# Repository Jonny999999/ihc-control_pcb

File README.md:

Repo for designing a custom pcb that controlls the electrical components of an IHC-Tractor.

# TOC
- [Links](#links)
- [Overview](#overview)
- [Open Schematic and Layout](#open-schematic-and-layout)
- [Connector Pin-assignment](#connector-pin-assignment)
  * [New Connectors](#new-connectors)
  * [Old Connectors](#old-connectors)
- [I/O List](#i-o-list)
  * [Switches](#switches)
  * [Relays](#relays)
- [Instructions (milling process)](#instructions--milling-process-)
  * [Step 1: export files](#step-1--export-files)
  * [Step 2: generate gcode (holes, traces, outline)](#step-2--generate-gcode--holes--traces--outline-)
  * [Step 3: generate gcode (engraving text)](#step-3--generate-gcode--engraving-text-)
  * [Step 4: mill outline](#step-4--mill-outline)
  * [Step 5: post processing](#step-5--post-processing)
- [Notes for next version (pcb design)](#notes-for-next-version--pcb-design-)
- [Notes for next pcb (milling)](#notes-for-next-pcb-milling)
  * [CNC-Control (WinPC-NC)](#cnc-control--winpc-nc-)
    + [Parameters](#parameters)
    + [Occurred problems](#occurred-problems)
  * [G-code generation (pcb2gcode)](#g-code-generation--pcb2gcode-)
    + [Notes for next time](#notes-for-next-time-)
    + [Gerber export (kicad)](#gerber-export--kicad-)

# Links
- Project documentation: https://pfusch.zone/control-pcb
- Firmware repo: https://github.com/Jonny999999/ihc-control_fw

# Overview
### Schematic
[pcb-ihc_schem_v4-milled-v1.1.pdf](/kicad/export/pcb-ihc_schem_v4-milled-v1.1.pdf)

### PCB-layout

# Open Schematic and Layout
Install kicad and open /kicad/pcb-ihc_kicad.kicad_pro  

For quickly viewing the current schematic and layout without installing kicad see exported files in
`kicad/export` or complete documentation at https://pfusch.zone

# Connector Pin-assignment
## New Connectors
See plan in firmware repo: 
https://github.com/Jonny999999/ihc-control_fw/blob/master/connection-plan.pdf

## Old Connectors
### 2 Pole connector 6mm2:
- 1: Starter motor (9)
- 2: Glowplug

### 6 Pole PC (3)
- 1: empty
- 2: Front light right, left (top right)
- 2a: Switch brakelight LS 1/2
- 3: Horn 1/2
- 3a Switch brakelight LS 2/2
- 4: Light left AL, right AR (bottom right)

### 6 Pole PB (2)
- 1: (20) Starter motor (relay) (top left)
- 2: (22) Fuel sensord
- 3: (24) Horn 2/2
- 4: (26) Oil pressure (switch to gnd)
- 5: (28) Temperature sensor
- 6: (30) Voltage regulator alternator (?)

### 6 Pole PA (1)
- 1: (31,32) FD sidelight -> trailer connector
- 2: (37) LB LB Light left -> trailer connector
- 3: (90) Side light BR
- 4: (88) Side light BL
- 5: (43, 42) FA -> trailer connector
- 6: (48) LA light left -> trailer connector

# I/O List
List of required I/O pins for planning the board
## Switches
### Switch to GND (pullup input)
- S_Warning Lights
- S_TurnLeft  toggle
- S_TurnRight toggle
- S_HighBeam  momentary
- S_Warning Lights  toggle
- S_Horn

### Switch to 12V (pulldown input)
- S_ParkingLight
- S_LowBeam
- S_Brake

### Notes
- S_worklight !!! no input left?!

## Relays
- K_BlinkLeft
- K_BlinkRight
- K_ParkingLight
- K_LowBeam
- K_HighBeam
- K_Horn

# Instructions (milling process)
Machine used: Stepcraft 420
## Step 1: export files
- Kicad: Export/plot pcb to gerber files
  Note: Also export User1 layer (includes text for engraving)
- Kicad: Generate drill file
```
back=./in/pcb-ihc_kicad-B_Cu.gbr
front=./in/pcb-ihc_kicad-F_Cu.gbr
outline=./in/pcb-ihc_kicad-Edge_Cuts.gbr
drill=./in/pcb-ihc_kicad-PTH.drl
see config file: pcb2gcode/millproject
```

## Step 2: generate gcode (holes, traces, outline)
- run pcb2gcode: `ihc-control_pcb/pcb2gcode> pcb2gcode`  
  will use millproject file for parameters as default config

## Step 3: generate gcode (engraving text)
- Kicad: moved text to be engraved into pcb on separate layer (User1)
- Also export/plot User1 layer with other gerber files
- Use separate millproject_text parameter file with pcb2gcode
  `pcb2gcode --config millproject_text`
NOTE: also include outline and maybe front in that millproject, even though that output is not used. It is necessary that the origin fits, otherwise there will be an offset!
- The trick was to use a negative offest (almost half the line width) to get more or less clean characters
- Generates pcb2gcode/out/text/back.ngc
Note: check if there is an offset/scaling issue to other files (back, drill). last time text got engraved into traces even though it matched on the other side

## Step 4: mill outline
Was not necessary in this case because size already matched

## Step 5: post processing
- Slightly smooth copper layer of pcb using grinding wool
- Drill holes for big 4mm2 2-pin terminals to 1.5mm if drilled with just 1mm on cnc

# Notes for next version (pcb design)
- Add resistor and diode for slowly charging the input capacitor (limit charging current)
- Add diode and/or jumper for isp programmer. Noticed that current is flowing from board 5v to programmer (input resistor got hot - only when programme connected) (alternatively jumper on programmer can be used for this...)
- ADD FUSES
  - Add fuse for 12v supply to 5v regulator
  - Fuses for mosfets?
  - Fuses for relay?
- Add mounting holes / at least make some space for third hole
- Slightly smaller size for easier cnc-milling

# Notes for next pcb milling
## CNC-Control (WinPC-NC)
### Parameters
- WinPC-NC has weird default z coorinates direction
  => **Z coordinates have to be inverted (!!!!!)** (otherwise will crash)
  -> parameters -> dateiformat -> z-koordinaten invertieren
- Change units to mm/min instead of default mm/s
### Occurred problems
- Problem Stepper not moving, only producing noise, but winpc-nc actually thinks that it moved coordinates - especially happened for Z-Axis
  - Solution 1: remove top section of gcode (simple G1 commands worked - see gcode generated with estlcam that is compatible)
  - Solution 2: switch from windows in Virtualbox to native windows

## G-code generation (pcb2gcode)
### notes for next time:
TODO: merge this section with milling instructions?
- Text engraving: slightly reduce Z depth 
- Zero Z-axis on multiple places: 
  At 2 edges pcb material was apparently lower, thus only scratched the surface -> had to mill again
- Zero-XY NOT at file origin! (the offset is caused by outline cutter diameter) 
  - 1. Load outline gcode, zero x,y next to border (note offset) 
  - 2. Confirm with moving on other side of pcb
- Make screenshot of absolute coordinates of origin (in case of accidential shift / position loss)
- Check position before drilling holes
- Fixing the pcb: Screws around the pcb are probably enough (check bend)
- When generating gcode for text separately, also include at least outline, otherwise there is an offset (origin makes no sense)

### Gerber export (kicad)
- design pcb slightly smaller for more tolerance...
- define custom origin 
  => tried this, setting "drill/place file origin" and tick the checkbox at plot, but had no effect to pcb2gcode in any way
- check if origin is the same in every gerber/gcode file (verify with gcode viewer?)

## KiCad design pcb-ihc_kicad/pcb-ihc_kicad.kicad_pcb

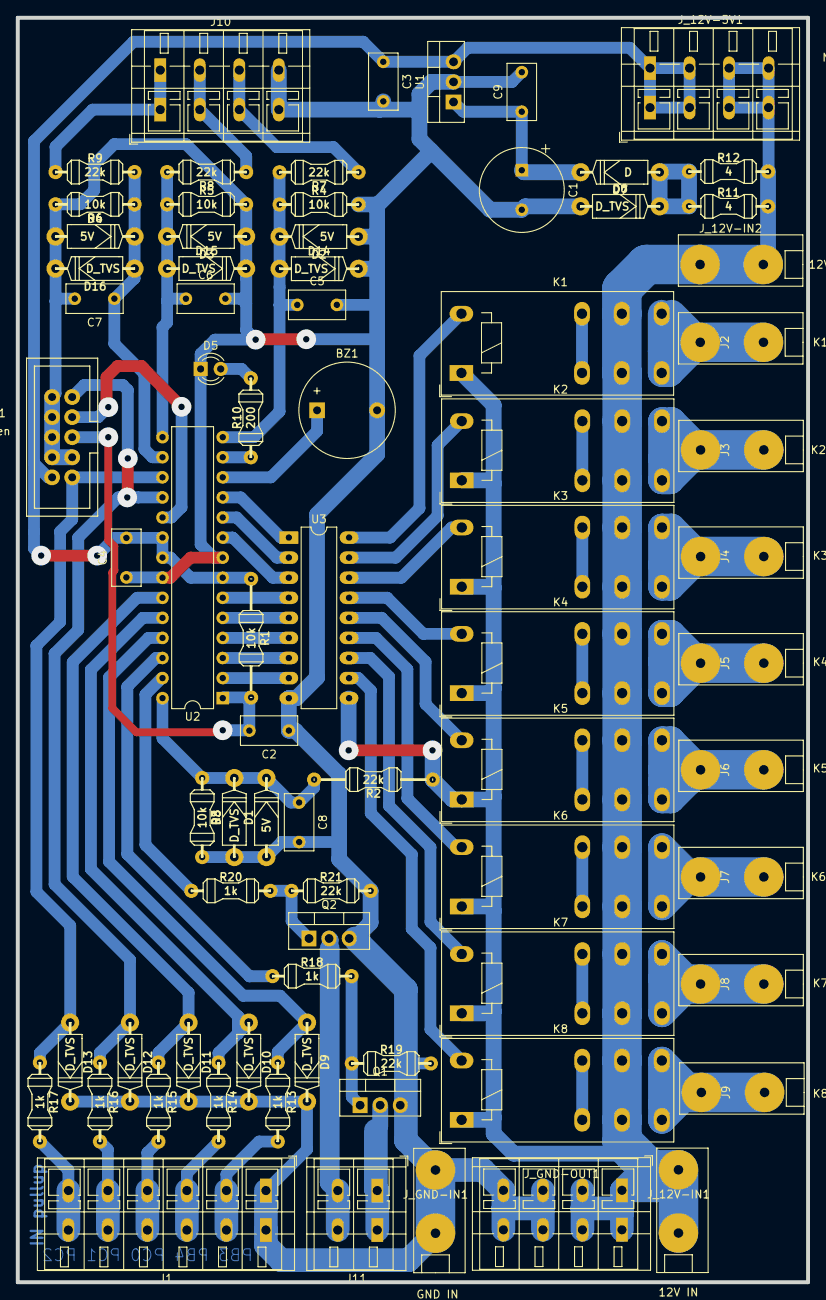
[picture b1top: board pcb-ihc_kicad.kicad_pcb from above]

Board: 2 copper layers, 100.0 x 160.0 mm, 77 parts (0 on the bottom side), 57 nets.

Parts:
BZ1: Buzzer - PD6; Buzzer_12x9.5RM7.6
C1: 100uF; CP_Radial_Tantal_D10.5mm_P5.00mm
C2, C3, C4, C5, C6, C7, C8: 100nF; C_Rect_L7.0mm_W3.5mm_P5.00mm
C9: 0.3uF; C_Rect_L7.0mm_W3.5mm_P5.00mm
D1, D2, D3, D4: 5V; my_D10_11
D5: LED - PD7; LED_D3.0mm
D6, D8, D9, D10, D11, D12, D13, D14, D15, D16: D_TVS; my_D10_11
D7: D; my_D10_11
J1: D-IN with pullup; TerminalBlock_WAGO_236-406_1x06_P5.00mm_45Degree
J2: K1 - PD5; my_KlemmeWago2604-single
J3: K2 - PB7; my_KlemmeWago2604-single
J4: K3 - PB6; my_KlemmeWago2604-single
J5: K4 - PD4; my_KlemmeWago2604-single
J6: K5 - PD3; my_KlemmeWago2604-single
J7: K6 - PD2; my_KlemmeWago2604-single
J8: K7 - PD1; my_KlemmeWago2604-single
J9: K8 - PD0; my_KlemmeWago2604-single
J10: D-IN with pulldown; TerminalBlock_WAGO_236-404_1x04_P5.00mm_45Degree
J11: 2x N-Mosfet; TerminalBlock_WAGO_236-402_1x02_P5.00mm_45Degree
J_12V-5V1: 2x 5V out, 2 x 12V out; TerminalBlock_WAGO_236-404_1x04_P5.00mm_45Degree
J_12V-IN1: 12V IN; my_KlemmeWago2604-single
J_12V-IN2: 12V IN (support); my_KlemmeWago2604-single
J_GND-IN1: GND IN; my_KlemmeWago2604-single
J_GND-OUT1: 2x GND out, 2x 12V out; TerminalBlock_WAGO_236-404_1x04_P5.00mm_45Degree
J_ISP-Programmer1: Conn_02x05_Odd_Even; my_wannenstecker_2x5
K1, K2, K3, K4, K5, K6, K7, K8: RT314A24; Relay_SPDT_Schrack-RT1-16A-FormC_RM5mm
Q1, Q2: IRFZ24N; TO-220-3_Vertical
R1: 10k; my_R15-long
R2: 22k; my_R15-long
R3, R4, R5, R6: 10k; my_R10
R7, R8, R9, R19, R21: 22k; my_R10
R10: 200; my_R10
R11, R12: 4; my_R10
R13, R14, R15, R16, R17, R18, R20: 1k; my_R10
U1: LM7805_TO220; TO-220-3_Vertical
U2: ATmega8-16P; DIP-28_W7.62mm
U3: ULN2803A; DIP-18_W7.62mm_LongPads

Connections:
+5V: C3.1, C4.2, J_12V-5V1.1, J_12V-5V1.2, J_ISP-Programmer1.2, R1.1, U1.3 (VO), U2.7 (VCC), U2.20 (AVCC), U2.21 (AREF)
+12V: J_12V-5V1.3, J_12V-5V1.4, J_12V-IN1.1, J_12V-IN2.1, J_GND-OUT1.1, J_GND-OUT1.2, K1.11, K1.A1, K2.11, K2.A1, K3.11, K3.A1, K4.11, K4.A1, K5.11, K5.A1, K6.11, K6.A1, K7.11, K7.A1, K8.11, K8.A1, R2.1, R11.2, R12.2, U3.10 (COM)
/Analog U_supply: C8.1, D1.1 (K), D8.1 (A1), R2.2, R3.1, U2.28 (PC5)
/IN pulldown 1: C5.1, D2.1 (K), D14.2 (A2), R4.1, R7.2, U2.14 (PB0)
/IN pulldown 2: C6.1, D3.1 (K), D15.2 (A2), R5.1, R8.2, U2.15 (PB1)
/IN pulldown 3: C7.1, D4.1 (K), D16.2 (A2), R6.1, R9.2, U2.16 (PB2)
/IN pullup 1: D13.2 (A2), J_ISP-Programmer1.1, R17.1, U2.17 (PB3)
/IN pullup 2: D12.2 (A2), J_ISP-Programmer1.9, R16.1, U2.18 (PB4)
/IN pullup 3: D11.2 (A2), R15.1, U2.23 (PC0)
/IN pullup 4: D10.2 (A2), R14.1, U2.24 (PC1)
/IN pullup 5: D9.2 (A2), R13.1, U2.25 (PC2)
/ISP-Reset: C2.2, J_ISP-Programmer1.5, R1.2, U2.1 (PC6/~RESET)
/ISP-SCK: J_ISP-Programmer1.7, U2.19 (PB5)
/Mosfet 1: R18.1, U2.26 (PC3)
/Mosfet 2: R20.1, U2.27 (PC4)
/ULN-I1: U2.11 (PD5), U3.1 (I1)
/ULN-I2: U2.10 (PB7/XTAL2), U3.2 (I2)
/ULN-I3: U2.9 (PB6/XTAL1), U3.3 (I3)
/ULN-I4: U2.6 (PD4), U3.4 (I4)
/ULN-I5: U2.5 (PD3), U3.5 (I5)
/ULN-I6: U2.4 (PD2), U3.6 (I6)
/ULN-I7: U2.3 (PD1), U3.7 (I7)
/ULN-I8: U2.2 (PD0), U3.8 (I8)
/buzzer: BZ1.1 (-), U2.12 (PD6)
/led: R10.1, U2.13 (PD7)
GND: BZ1.2 (+), C1.2, C2.1, C3.2, C4.1, C5.2, C6.2, C7.2, C8.2, C9.2, D1.2 (A), D2.2 (A), D3.2 (A), D4.2 (A), D5.1 (K), D6.2 (A2), D8.2 (A2), D9.1 (A1), D10.1 (A1), D11.1 (A1), D12.1 (A1), D13.1 (A1), D14.1 (A1), D15.1 (A1), D16.1 (A1), J1.1, J10.4, J_GND-IN1.1, J_GND-OUT1.3, J_GND-OUT1.4, J_ISP-Programmer1.3, J_ISP-Programmer1.4, J_ISP-Programmer1.6, J_ISP-Programmer1.8, J_ISP-Programmer1.10, Q1.3 (S), Q2.3 (S), R3.2, R4.2, R5.2, R6.2, R19.2, R21.2, U1.2 (GND), U2.8 (GND), U2.22 (AGND), U3.9 (GND)
unnamed: C1.1, C9.1, D7.1 (K), U1.1 (VI)
unnamed: D5.2 (A), R10.2
unnamed: D6.1 (A1), D7.2 (A), R11.1, R12.1
unnamed: J1.2, R13.2
unnamed: J1.3, R14.2
unnamed: J1.4, R15.2
unnamed: J1.5, R16.2
unnamed: J1.6, R17.2
unnamed: J2.1, K1.14
unnamed: J3.1, K2.14
unnamed: J4.1, K3.14
unnamed: J5.1, K4.14
unnamed: J6.1, K5.14
unnamed: J7.1, K6.14
unnamed: J8.1, K7.14
unnamed: J9.1, K8.14
unnamed: J10.1, R9.1
unnamed: J10.2, R8.1
unnamed: J10.3, R7.1
unnamed: J11.1, Q1.2 (D)
unnamed: J11.2, Q2.2 (D)
unnamed: K1.A2, U3.18 (O1)
unnamed: K2.A2, U3.17 (O2)
unnamed: K3.A2, U3.16 (O3)
unnamed: K4.A2, U3.15 (O4)
unnamed: K5.A2, U3.14 (O5)
unnamed: K6.A2, U3.13 (O6)
unnamed: K7.A2, U3.12 (O7)
unnamed: K8.A2, U3.11 (O8)
unnamed: Q1.1 (G), R18.2, R19.1
unnamed: Q2.1 (G), R20.2, R21.1

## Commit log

2022-04-04 init
    pcb layout is in progress, schematic needs optimizations
2022-04-04 Add 2x Mosfet, Change labels, Change layout
2022-04-04 Optimize layout
2022-04-04 Routing first version ready for validation
    in this commit the entire routing of tracks was done. next step
    validation and optimizations.
2022-04-05 Optimize routing and layout
    - fix track width on several locations (1.5 to 2mm)
    - minor changes in routing
    - move relays closer together
    - add additional 12V input terminal
2022-04-05 Add gitignore, remove backups
    Add gitignore to ignore auto-save and backup files from kicad
2022-04-05 Add terminal descriptions, Clean up schematic
    - Add detailed terminal/connector descriptions (e.g. which uC pin)
    - Positioned labels in layout outside of pcb
    - cleanup in schematic reorder groups, fix boxes...
2022-04-06 Swap Layers Front/Back Tracks
    Noticed in 3d viewer that tracks were on the same side as components...
    swaped F.Cu and B.Cu using " Edit -> Swap layers ". Now tracks are on
    the other side...
2022-04-07 Add text to copper back layer
    Add description of terminals (desc, controller pin) as text to copper
    layer. The plan is that the text is actually milled onto the pcb
    (like tracks)
2022-04-07 Add pcb2gcode
    Created folder for pcb2gcode (to convert gerber files from kicad to
    gcode for winpc)
    Add config file
    tried to extract parameters from old gcode files of electric kart
    project (also converted with pcb2gcode)
    worked with pcb2gcode gui for some time but noticed it is quite
2022-04-07 Renamed kicad folder
    renamed folder pcb-ihc_kicad to kicad (project folder name describes
    project anyways)
2022-04-08 Add Readme, Add ihc-schematic
    Add readme for notes about the project
    Add downloaded ihc schematic for identification of pins
2022-04-08 Add gcode file for milling 162x102 plane for pcb
    copied old file generated using estlcam that mills an area 162x102mm
    0.7mm deep using a 6mm cutter
2022-04-09 Remove and ignore svg files of pcb2gcode from git
2022-04-09 Move text to User1 layer, adjust positions
    Move text that should be engraved to pcb from copper-back layer to user1
    layer (=> can be handled / processed separately with other parameters by
    pcb2gcode)
    also make line width to 0.3 for previous smaller text
2022-04-09 pcb2gcode: Add millproject_text config
    Add separate parameter file for engraving text using separate exported User1
    layer
2022-04-09 pcb2gcode: Change several parameters: zsafe, feed, drill...
    change zsafe from 5 to 2mm (z takes too long to move - faster)
    change zchange from 40 to 30 (unnecessary high exceeded working range
    when test-milling in air)
    change millfeed from 300 to 500 (appeared to slow - more room for adjustments to greater speeds while milling 0-200%)
    add drills avaialbe=0.8,1 (drilling with those diameters ony anyways -
    no unnecessary tool changes that get skipped anyways)
2022-04-09 readme: pcb2gcode details, IHC-schematic interpretation
    Tried to identify connector pins using ihc schematic
    Added description of engraving text using kicad and pcb2gcode
2022-04-09 Generated gcode of current pcb version
2022-04-09 First milling: Update readme, gcode files
    First pcb got produced, there were several issues - see readme "notes
    for next time milling"
    gcode for text engraving is apparently scaled wrong? does not line up at
    the other side of pcb - this has to be looked into
2022-04-10 Reduce length of pcb
    Layout: move top components closer together to have more "free space" on
    the top thus more tolerance when milling
2022-04-10 pcb2gcode: Change outline side and cutter-diameter
    cutter diameter caused offset of origin in gcode files, which was quite
    confusing at first try. changed from 3mm to 0mm in both millproject and
    millproject_text
    changed cute-side to back, default was front which mirrored the gcode
    (wrong origin position)
2022-04-10 Minor optimization of text position
2022-04-10 Generate gcode for second milling procedure
    Exported gerber files from current pcb layout
    generated gcode with applied optimizations learned from last milling
2022-04-10 Fix incorrect label/text 'PB2' <> 'PB0'
    The description of input terminal "in pulldown" was inverted
    Fix order on User1 layer and F.Fab in pcbnew
2022-04-11 Update readme: Add notes for next version
2022-05-07 Update readme: Add nots for next version (layout)
    Fix formatting for schematic headlines
    Add further notes about pcb layout design optimizations (fuses, mounting holes)
2023-09-25 Update README, Add export folder, schematic
    Add export folder with schematic and layout screenshots
    Update Readme: translate to english, add TOC, cleanup
2023-12-08 Update readme: Add images, Update toc
